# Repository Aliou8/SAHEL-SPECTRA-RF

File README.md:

# SAHEL-CUBESAT: An Experimental Educational CubeSat 
# Project work in progress

This project aims to develop a complete experimental CubeSat for educational purposes. It is based on an STM32H7 MCU for data handling and uses two CC1200 radios for communication. The software is developed using a Zephyr-like RTOS.

<table>  <tr>    <td align="center">      <br>      <b>Mechanical Frame</b>    </td>    <td align="center">      <br>      <b>CubeSat Assembly with PCBs</b>    </td>    <td align="center">      <br>      <b>Complete CubeSat Assembly</b>    </td>  </tr></table>

## Table of Contents

- [Hardware](#hardware)
  - [Structure](#structure)
  - [Electronics](#electronics)
    - [Radio and OBC PCB](#radio-and-obc-pcb)
    - [Solar Panel and Battery PCB](#solar-panel-and-battery-pcb)

- [Software](#software)
  - [System Logic](#system-logic)
  - [Implementation](#implementation)

- [Ground Station Communication](#ground-station-communication)

---

## Hardware

### Structure

The structure was designed according to the specifications using [Onshape](https://cad.onshape.com?utm_source=chatgpt.com). All printable components can be found in this [directory](hardware/structure/).
<table>  <tr>    <td align="center">      <br>      <b>Mechanical faces X+ X- Y+ Y-</b>    </td>    <td align="center">      <br>      <b>Mechanical faces Z+ Z-</b>    </td>    <td align="center">      <br>      <b> Solar panel</b>    </td>  </tr></table>

---

### Electronics

KiCad is used for the electronic design. The hardware is divided into three parts. The first part includes the radio communication system and the OBC (On-Board Computer) for the CubeSat. The second part consists of a board integrating several sensors and a solar MPPT controller IC.

#### Radio and OBC PCB : Available in: [hardware/sahel_pcb_main](hardware/sahel_pcb_main/)

<table>
  <tr>
    <td align="center">
      <br>
      <b>Architectural Diagram of the Radio and OBC PCB</b>
    </td>
    <td align="center">
      <br>
      <b>Radio and OBC PCB</b>
    </td>
  </tr>
</table>

---

##### Components

###### MCU

**STM32H7B0VBTx**  
High-performance Arm Cortex-M7 MCU with DSP and DP-FPU, 128 KB Flash, 1,376 KB SRAM, up to 280 MHz.

---

###### FRAM — FM24CL64B

| Parameter        | Value            |
|-----------------|------------------|
| Memory          | 64-Kbit (8K × 8) |
| I2C Address      | `0b1010000`        |
| SDA (I2C3)       | PC9              |
| SCL (I2C3)       | PA8              |
| Write Protect    | PC5              |

###### Sensors

**Accelerometer, Gyroscope, and Magnetometer: LSM9DS1**  
**Barometer: BMP388**

| Parameter            | Value        |
|---------------------|-------------|
| I2C Address (ACC/GYRO) | `0b1101011` |
| I2C Address (MAG)      | `0b0011110` |
| I2C Address (BARO)     | `0b1110111` |
| SDA (I2C4)             | PD13        |
| SCL (I2C4)             | PD12        |
| INT_ACC/GYRO           | PE8         |
| DRDY_MAG               | PE7         |
| DRDY_BARO              | PB2         |
---

###### RTC & Temperature Sensor

**RTC: RV-8803-C7**  
**TEMP: TMP100**

| Parameter        | Value            |
|-----------------|------------------|
| RTC I2C Address  | `0b0110010`        |
| TEMP I2C Address | `0b1001000`        |
| SDA (I2C1)       | PB7              |
| SCL (I2C1)       | PB6              |
| RTC_INT          | PB5              |
| RTC_EVI          | PB4              |

---

###### CAN Interface: TCAN334G

| Signal     | Pin  |
|-----------|------|
| CAN1_TX    | PD1  |
| CAN1_RX    | PD0  |
| CAN_SHDN   | PA15 |
| CAN_STBY   | PD2  |

---

###### RS-485 Interface: ISL3170E

| Signal      | Pin  |
|------------|------|
| UART2_RX    | PD6  |
| UART2_TX    | PD5  |
| UART2_EN    | PD4  |

---
###### Radio Interface: CC1200

The CC1200 device is a fully integrated single-chip radio transceiver designed for high performance at very low-power and low-voltage operation in cost-effective wireless systems frequency bands at 164–192 MHz, 274–320 MHz, 410–480 MHz, and 820–960 MHz.

**UHF(TX/RX) 420-470 MHz**

| Signal      | Pin  |
|------------|------|
| UHF_SCK(SPI1)    | PA5  |
| UHF_MISO(SPI1)     | P6  |
| UHF_MOSI(SPI1)     | P7  |
| UHF_CS(SPI1)     | PA4  |
| UHF_GPIO2    | PC5  |
| UHF_GPIO3    | PC4  |

**VHF(TX/RX) 164-192 MHz**

| Signal      | Pin  |
|------------|------|
| UHF_SCK(SPI4)    | PE12  |
| UHF_MISO(SPI4)     | PE13  |
| UHF_MOSI(SPI4)     | PE14  |
| UHF_CS(SPI4)     | PE11  |
| UHF_GPIO2    | PB10  |
| UHF_GPIO3    | PE14  |

#### Solar Panel and Battery PCB

<table>
  <tr>
    <td align="center">
      <br>
      <b> Solar charger PCB </b>      
    </td>
    <td align="center">
      <br>
      <b> Battery charger PCB </b>
    </td>
  </tr>
</table>

In this project, the BQ24650 solar charger is used together with an INA219A current sensor for photovoltaic (IPV) monitoring.

| Parameter                  | Value               |
|---------------------------|---------------------|
| Input Voltage (Vin)       | 9V – 24V            |
| MPPT Voltage (VMPPT)      | 9V                  |
| Charge Voltage            | 8.2V                |
| Charge Current            | 1.2A                |
| Precharge Current         | 125mA               |
| Termination Current       | 125mA               |
| INA219A I2C Address       | `0b1000010`         |
| SDA (I2C4)                | PD13                |
| SCL (I2C4)                | PD12                |

---

### Battery Pack & Protection

The system uses four RS PRO Li-Ion batteries configured in a 2S2P arrangement with the following specifications:

| Parameter                          | Value                |
|-----------------------------------|----------------------|
| Nominal Voltage                   | 3.60V                |
| Capacity                          | 3500mAh              |
| Maximum Charge Voltage            | 4.20V                |
| Energy                            | 12.60Wh              |
| Operating Voltage                 | 4.20V – 2.50V        |
| Cut-Off Voltage                   | 2.50V                |
| Standard Charge Method            | CC-CV                |
| Standard Charge Current           | 0.2C (0.7A)          |
| Standard Charge Cut-Off Current   | 0.02C (0.07A)        |
| Maximum Continuous Charge Current | 1.0C (3.5A)          |

#### Standard Discharge Conditions

| Temperature Range | Discharge Current |
|------------------|------------------|
| 0°C – 10°C       | 0.1C (0.35A)     |
| 10°C – 20°C      | 0.2C (0.7A)      |
| 20°C – 45°C      | 0.5C (1.75A)     |

The battery protection and monitoring system is based on the BQ76907 battery monitor IC and an INA219A current sensor.

| Parameter              | Value                    |
|-----------------------|--------------------------|
| I2C Address (BQ76907) | `0b0001000` (default)    |
| I2C Address (INA219A) | `0b1000000`              |
| SDA (I2C1)            | PB7                      |
| SCL (I2C1)            | PB6                      |
| Battery Alert         | PE2                      |

---

## Software

The software is developed using **Zephyr RTOS**.  
The middleware architecture is described in the [Software Documentation](software/README.md).

---

## System Logic

We are developing the system based on **Zephyr RTOS**, using a **multi-threaded architecture** combined with **Zephyr zbus** for internal communication.

The application is structured around multiple independent threads that communicate through the **zbus message bus system**.

### Key concepts:
- Each module acts as a **zbus publisher and/or subscriber**
- Data is exchanged through **well-defined channels**
- This avoids tight coupling between components
- Improves scalability and modularity of the system

### Benefits of using zbus:
- Decoupled architecture between threads
- Clean publish/subscribe communication model
- Easier debugging and tracing of data flow
- Better maintainability for complex systems

---

## Ground Station Communication

The ground station software is **not yet implemented**.  
The current plan is to develop it using either:
- **Qt-based applications** (for a custom GUI control station)
- or existing **SDR software tools** for signal reception and analysis

---

## Communication Mechanism

The communication between the system and the ground station is designed around a structured and layered protocol stack.

### 1. Physical & Link Layer
The system uses the **AX.25 protocol** as the primary data link layer.

AX.25 provides:
- reliable packet framing
- addressing capability (callsigns)
- error detection (CRC)
- compatibility with amateur radio / SDR systems

---

### 2. Packet Structure

All exchanged data is encapsulated in AX.25 frames containing:
- payload data
- message type identifier
- optional sequence number
- checksum (handled by AX.25 layer)

---

### 3. Command System

The ground station can send **commands** to the embedded system.

Commands are structured as:
- command ID
- optional parameters
- target module (if applicable)

Examples of command types:
- system control (start / stop / reset)
- configuration update
- request sensor data
- debug / diagnostics requests

---

### 4. Internal Routing (zbus integration)

Incoming and outgoing messages are bridged into the internal **zbus architecture**.

Flow:
- AX.25 frame received → decoded → converted to internal message
- message published on **zbus channel**
- relevant modules subscribe and react

---

### 5. Response System

The system responds using structured messages:
- ACK / NACK for command validation
- telemetry data packets
- event notifications
- status reports

All responses follow the same pipeline:
**zbus → encoder → AX.25 → ground station**

---

### 6. Design Goals

This architecture is designed to ensure:
- robustness over noisy RF links
- modular separation between communication and logic
- easy integration with SDR tools
- future compatibility with different ground station implementations

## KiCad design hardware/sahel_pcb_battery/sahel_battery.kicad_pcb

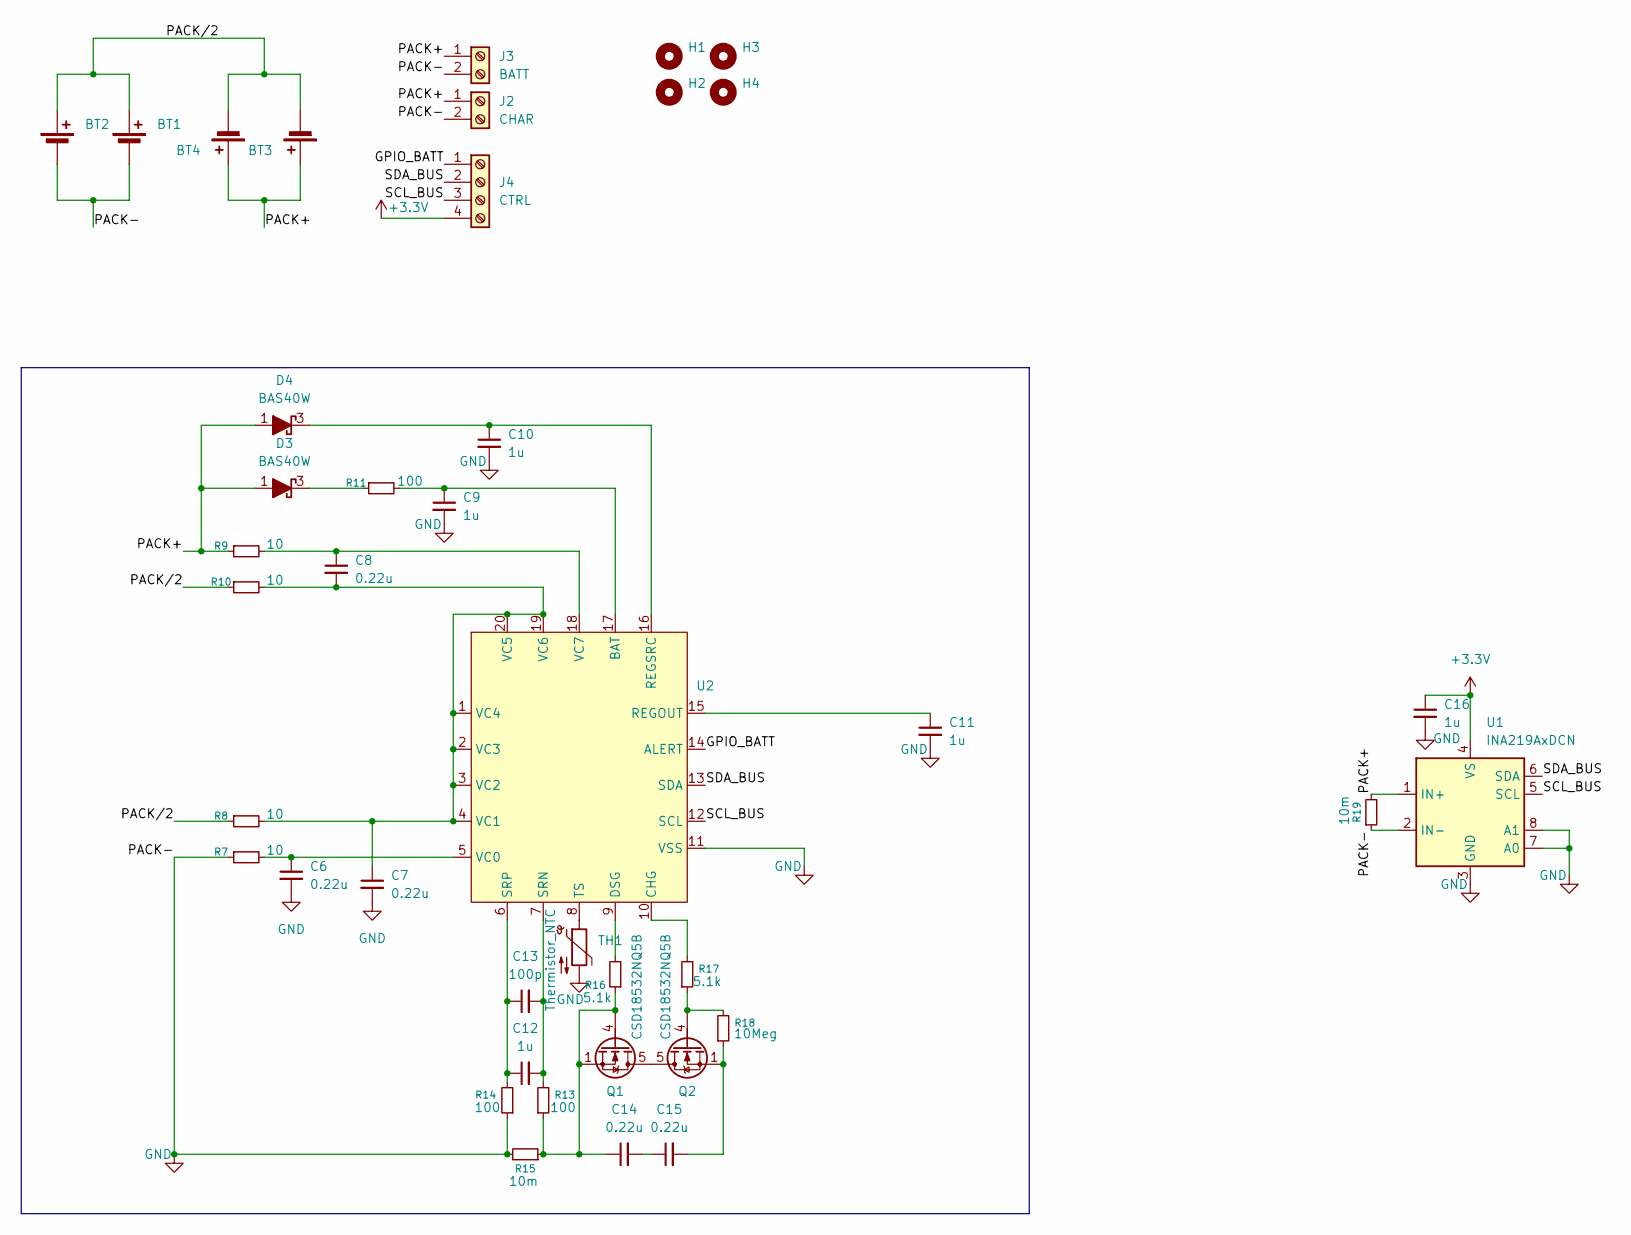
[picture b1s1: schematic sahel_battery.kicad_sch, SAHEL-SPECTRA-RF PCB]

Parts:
BT1, BT2, BT3, BT4: Battery_Cell; BatteryHolder_Keystone_1042_1x18650
C6, C7, C8, C14, C15: 0.22u; C_0805_2012Metric
C9, C10, C12: 1u; C_0805_2012Metric
C11, C16: 1u; C_0402_1005Metric
C13: 100p; C_0805_2012Metric
D3, D4: BAS40W; SOT-323_SC-70
H1, H2, H3, H4: MountingHole; MountingHole_2.5mm
J2: CHAR; JST_PH_B2B-PH-K_1x02_P2.00mm_Vertical
J3: BATT; JST_PH_B2B-PH-K_1x02_P2.00mm_Vertical
J4: CTRL; JST_PH_B4B-PH-K_1x04_P2.00mm_Vertical
Q1, Q2: CSD18532NQ5B; TDSON-8-1
R7, R8, R9, R10: 10; R_0805_2012Metric
R11, R13, R14: 100; R_0805_2012Metric
R15, R19: 10m; R_1206_3216Metric
R16, R17: 5.1k; R_0805_2012Metric
R18: 10Meg; R_0805_2012Metric
TH1: Thermistor_NTC; RV_Disc_D7mm_W3.4mm_P5mm
U1: INA219AxDCN; SOT-23-8
U2: QFN-20-1EP_3.5x3.5mm_P0.5mm_EP2x2mm

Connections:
+3.3V: C16.1, J4.4, U1.4 (VS)
/GPIO_BATT: J4.1, U2.14 (ALERT)
/PACK+: BT3.1 (+), BT4.1 (+), D3.1 (A), D4.1 (A), J2.1, J3.1, R9.1, R19.2, U1.1 (IN+)
/PACK/2: BT1.1 (+), BT2.1 (+), BT3.2 (-), BT4.2 (-), R8.1, R10.1
/SCL_BUS: J4.3, U1.5 (SCL), U2.12 (SCL)
/SDA_BUS: J4.2, U1.6 (SDA), U2.13 (SDA)
GND: BT1.2 (-), BT2.2 (-), C6.2, C7.2, C9.2, C10.2, C11.2, C16.2, J2.2, J3.2, R7.1, R14.1, R15.2, R19.1, TH1.2, U1.2 (IN-), U1.3 (GND), U1.7 (A0), U1.8 (A1), U2.11 (VSS), U2.21 (PAD)
unnamed: C14.2, C15.1
unnamed: C15.2, Q2.1 (S), Q2.2 (S), Q2.3 (S), R18.1
unnamed: D3.3 (K), R11.1
unnamed: C10.1, D4.3 (K), U2.16 (REGSRC)
unnamed: Q1.5 (D), Q2.5 (D)
unnamed: C14.1, Q1.1 (S), Q1.2 (S), Q1.3 (S), Q1.4 (G), R13.1, R15.1, R16.1
unnamed: Q2.4 (G), R17.1, R18.2
unnamed: C9.1, R11.2, U2.17 (BAT)
unnamed: R17.2, U2.10 (CHG)
unnamed: R16.2, U2.9 (DSG)
unnamed: C11.1, U2.15 (REGOUT)
unnamed: C12.2, C13.2, R13.2, U2.7 (SRN)
unnamed: C12.1, C13.1, R14.2, U2.6 (SRP)
unnamed: TH1.1, U2.8 (TS)
unnamed: C6.1, R7.2, U2.5 (VC0)
unnamed: C7.1, C8.2, R8.2, R10.2, U2.1 (VC4), U2.2 (VC3), U2.3 (VC2), U2.4 (VC1), U2.19 (VC6), U2.20 (VC5)
unnamed: C8.1, R9.2, U2.18 (VC7)

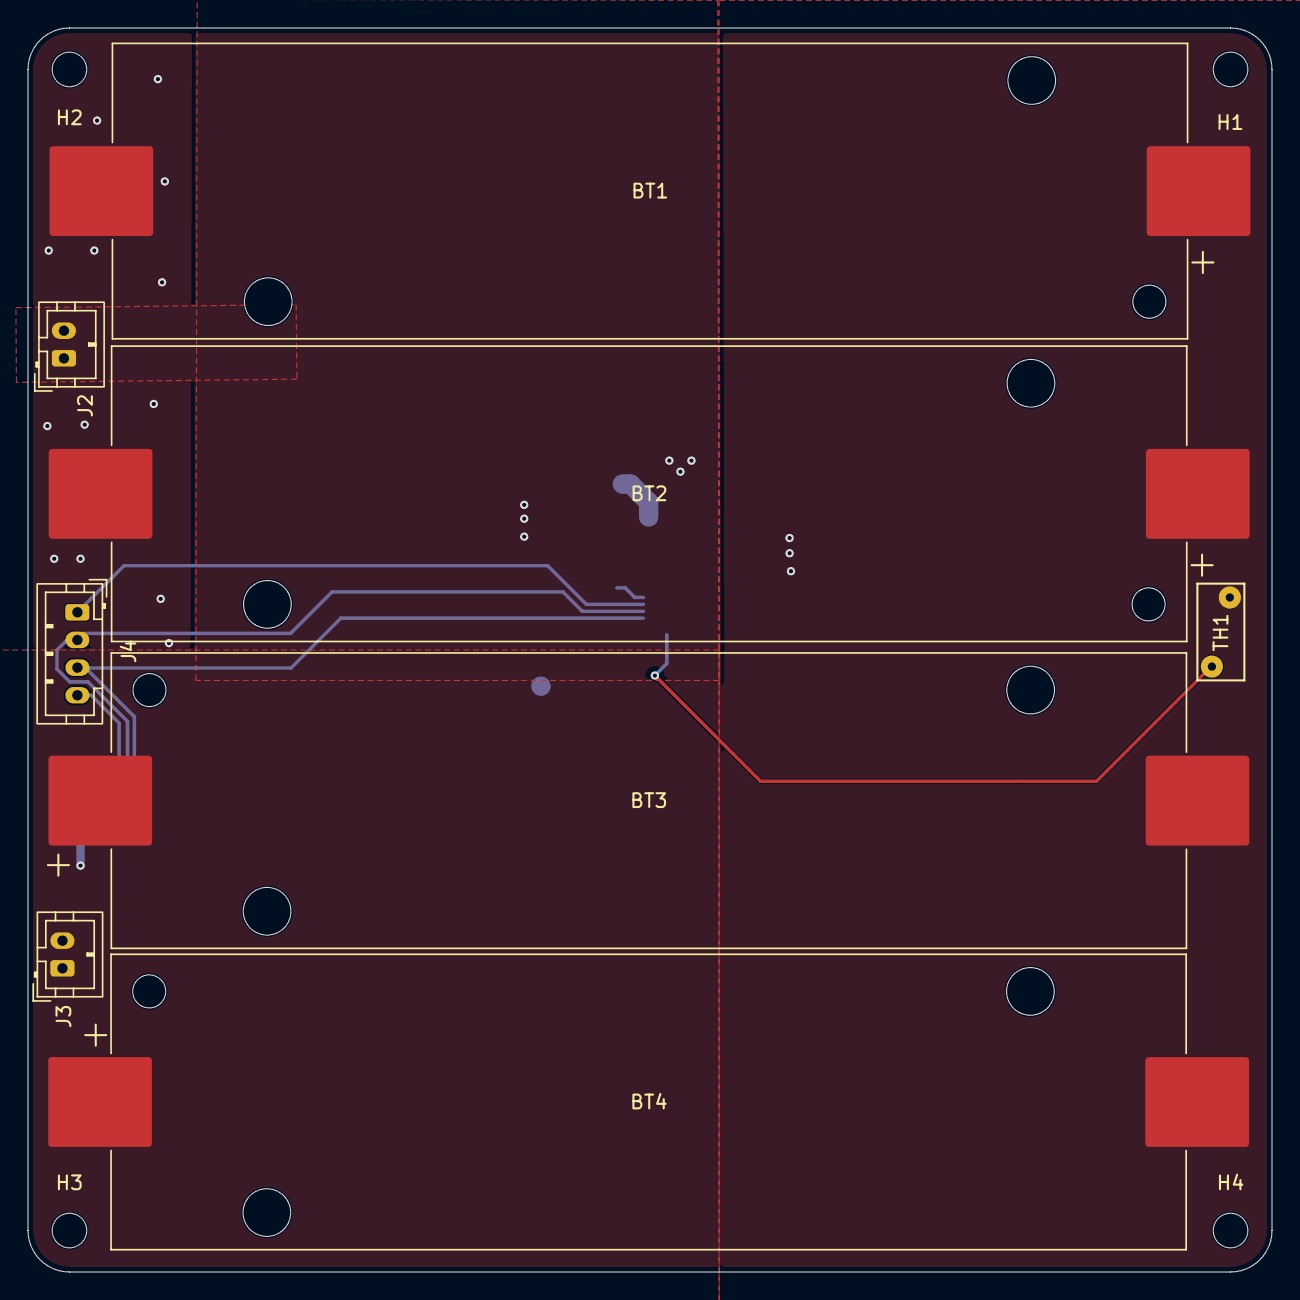
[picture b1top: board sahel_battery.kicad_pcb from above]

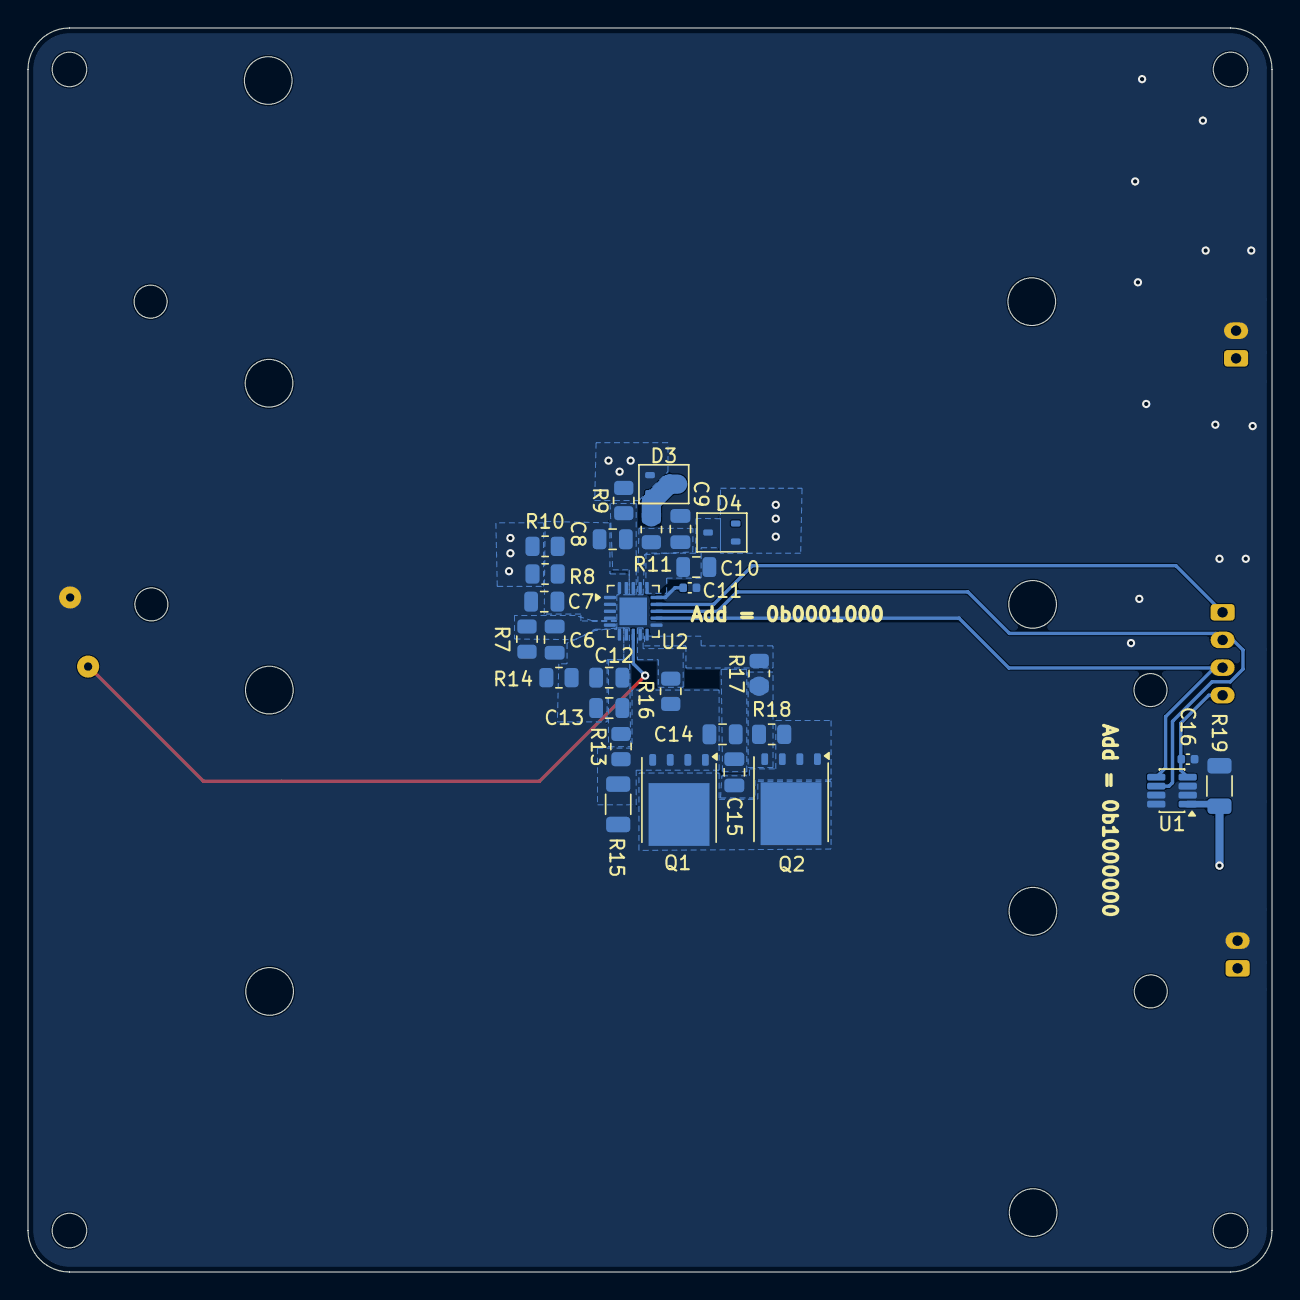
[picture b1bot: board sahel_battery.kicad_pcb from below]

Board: 2 copper layers, 90.0 x 90.0 mm, 41 parts (29 on the bottom side), 24 nets.

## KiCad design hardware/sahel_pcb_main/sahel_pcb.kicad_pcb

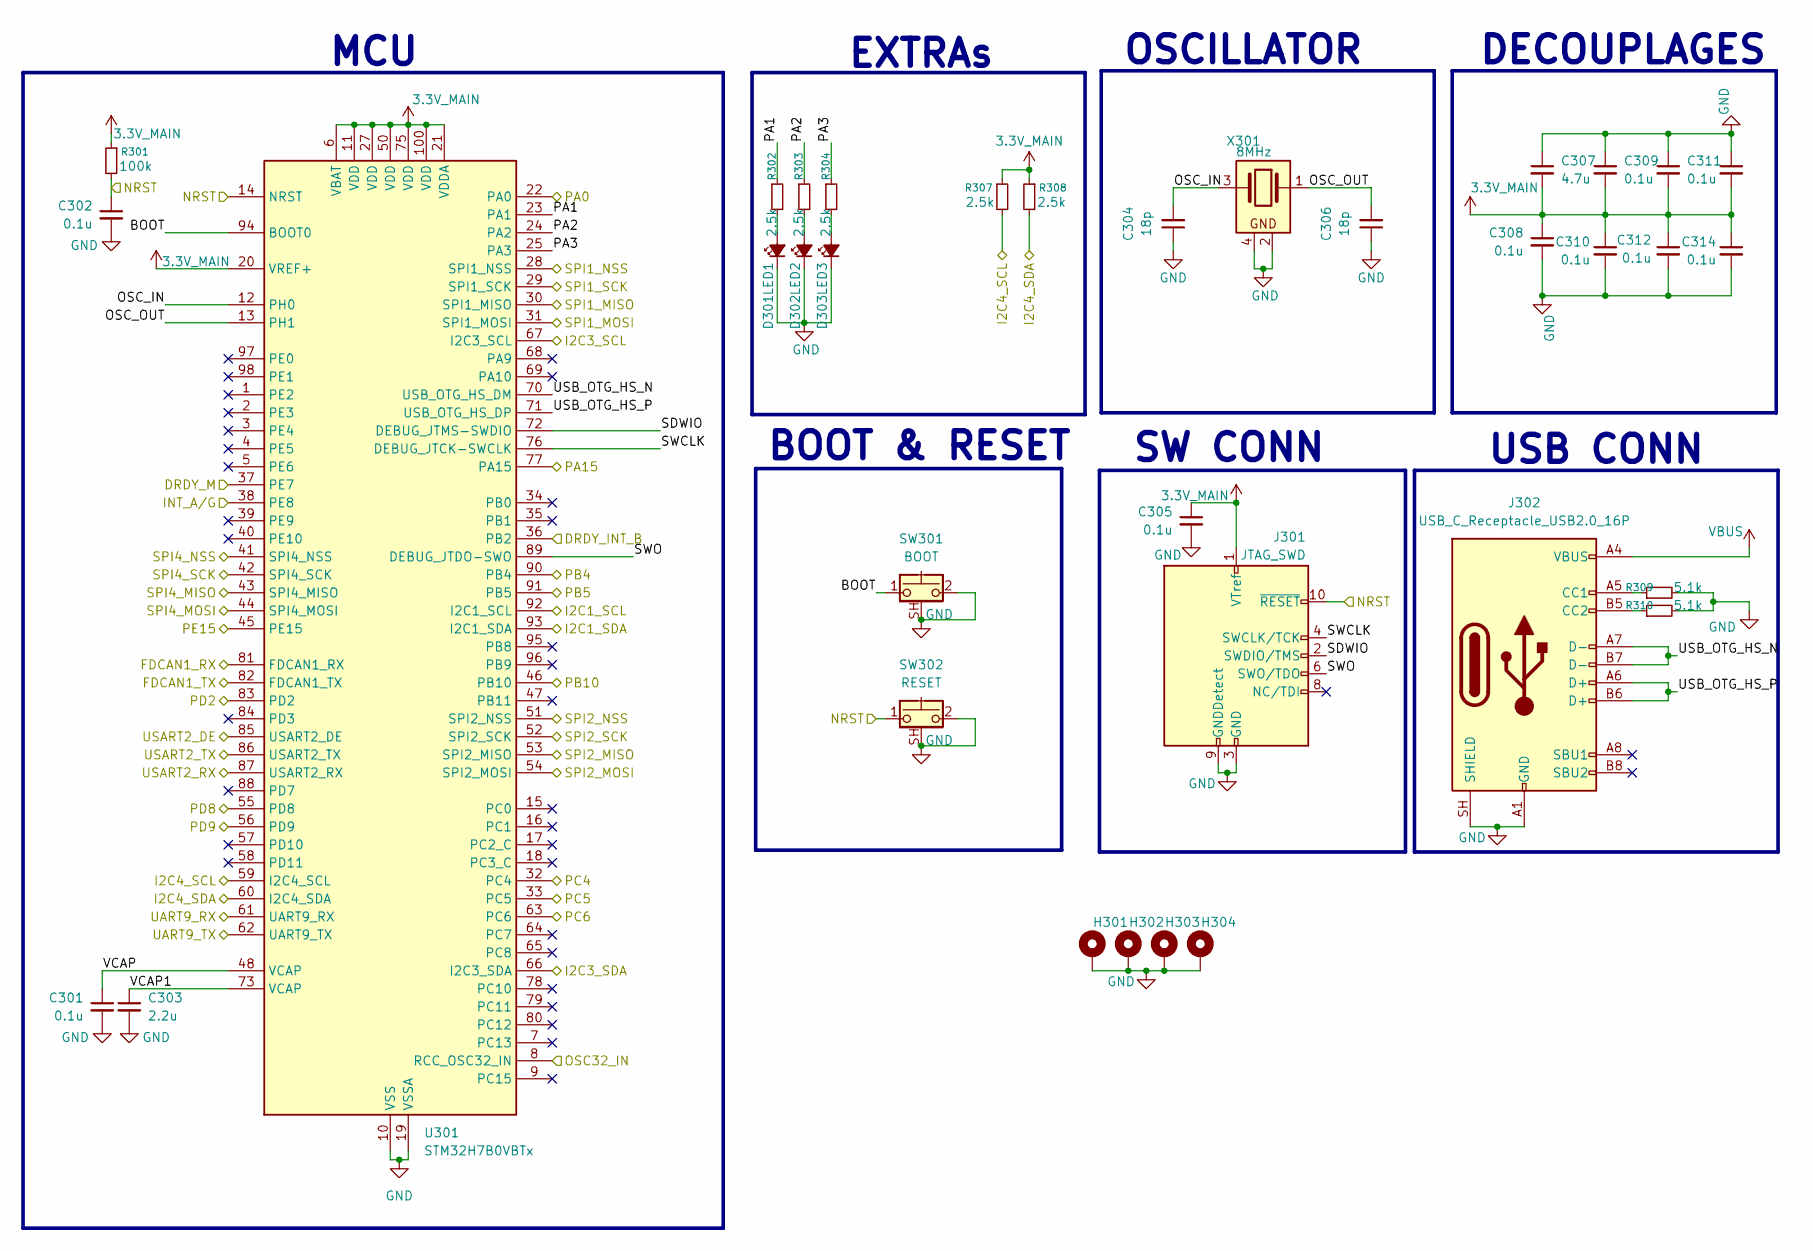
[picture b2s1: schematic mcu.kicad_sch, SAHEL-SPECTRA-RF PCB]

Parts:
C301, C302, C305, C308, C309, C310, C311, C312, C313, C314: 0.1u; C_0402_1005Metric
C303: 2.2u; C_0402_1005Metric
C304, C306: 18p; C_0402_1005Metric
C307: 4.7u; C_0402_1005Metric
D301: LED1; LED_0402_1005Metric
D302: LED2; LED_0402_1005Metric
D303: LED3; LED_0402_1005Metric
H301, H302, H303, H304: MountingHole_Pad; MountingHole_2.2mm_M2_Pad
J301: JTAG_SWD; PinHeader_2x05_P1.27mm_Vertical
J302: USB_C_Receptacle_USB2.0_16P; USB_C_Receptacle_GCT_USB4105-xx-A_16P_TopMnt_Horizontal
R301: 100k; R_0402_1005Metric
R302, R303, R304, R307, R308: 2.5k; R_0402_1005Metric
R309, R310: 5.1k; R_0402_1005Metric
SW301: BOOT; SW_SPST_CK_KMS2xxGP
SW302: RESET; SW_SPST_CK_KMS2xxGP
U301: STM32H7B0VBTx; LQFP-100_14x14mm_P0.5mm
X301: 8MHz; Crystal_SMD_2520-4Pin_2.5x2.0mm

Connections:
3.3V_MAIN: C305.1, C307.2, C308.1, C309.2, C310.1, C311.2, C312.1, C313.2, C314.1, J301.1 (VTref), R301.1, R307.1, R308.1, U301.6 (VBAT), U301.11 (VDD), U301.20 (VREF+), U301.21 (VDDA), U301.27 (VDD), U301.50 (VDD), U301.75 (VDD), U301.100 (VDD); also elsewhere on the board
/BUS_SCL: R307.2, U301.59 (I2C4_SCL); also elsewhere on the board
/BUS_SDA: R308.2, U301.60 (I2C4_SDA); also elsewhere on the board
/BUS_UART_RX: U301.61 (UART9_RX); also elsewhere on the board
/BUS_UART_TX: U301.62 (UART9_TX); also elsewhere on the board
/DRDY_INT_B: U301.36 (PB2); also elsewhere on the board
/DRDY_M: U301.37 (PE7); also elsewhere on the board
/INT_A/G: U301.38 (PE8); also elsewhere on the board
/MCU/BOOT: SW301.1, U301.94 (BOOT0)
/MCU/FDCAN1_RX: U301.81 (FDCAN1_RX); also elsewhere on the board
/MCU/FDCAN1_TX: U301.82 (FDCAN1_TX); also elsewhere on the board
/MCU/I2C3_SCL: U301.67 (I2C3_SCL); also elsewhere on the board
/MCU/I2C3_SDA: U301.66 (I2C3_SDA); also elsewhere on the board
/MCU/NRST: C302.1, J301.10 (~RESET), R301.2, SW302.1, U301.14 (NRST); also elsewhere on the board
/MCU/OSC32_IN: U301.8 (RCC_OSC32_IN); also elsewhere on the board
/MCU/OSC_IN: C304.2, U301.12 (PH0), X301.3
/MCU/OSC_OUT: C306.2, U301.13 (PH1), X301.1
/MCU/PA0: U301.22 (PA0); also elsewhere on the board
/MCU/PA1: R302.1, U301.23 (PA1)
/MCU/PA2: R303.1, U301.24 (PA2)
/MCU/PA3: R304.1, U301.25 (PA3)
/MCU/PA15: U301.77 (PA15); also elsewhere on the board
/MCU/PB4: U301.90 (PB4); also elsewhere on the board
/MCU/PB5: U301.91 (PB5); also elsewhere on the board
/MCU/PB10: U301.46 (PB10); also elsewhere on the board
/MCU/PC4: U301.32 (PC4); also elsewhere on the board
/MCU/PC5: U301.33 (PC5); also elsewhere on the board
/MCU/PC6: U301.63 (PC6); also elsewhere on the board
/MCU/PD2: U301.83 (PD2); also elsewhere on the board
/MCU/PE15: U301.45 (PE15); also elsewhere on the board
/MCU/SDWIO: J301.2 (SWDIO/TMS), U301.72 (DEBUG_JTMS-SWDIO)
/MCU/SPI1_MISO: U301.30 (SPI1_MISO); also elsewhere on the board
/MCU/SPI1_MOSI: U301.31 (SPI1_MOSI); also elsewhere on the board
/MCU/SPI1_NSS: U301.28 (SPI1_NSS); also elsewhere on the board
/MCU/SPI1_SCK: U301.29 (SPI1_SCK); also elsewhere on the board
/MCU/SPI4_MISO: U301.43 (SPI4_MISO); also elsewhere on the board
/MCU/SPI4_MOSI: U301.44 (SPI4_MOSI); also elsewhere on the board
/MCU/SPI4_NSS: U301.41 (SPI4_NSS); also elsewhere on the board
/MCU/SPI4_SCK: U301.42 (SPI4_SCK); also elsewhere on the board
/MCU/SWCLK: J301.4 (SWCLK/TCK), U301.76 (DEBUG_JTCK-SWCLK)
/MCU/SWO: J301.6 (SWO/TDO), U301.89 (DEBUG_JTDO-SWO)
/MCU/USART2_DE: U301.85 (USART2_DE); also elsewhere on the board
/MCU/USART2_RX: U301.87 (USART2_RX); also elsewhere on the board
/MCU/USART2_TX: U301.86 (USART2_TX); also elsewhere on the board
/MCU/USB_OTG_HS_N: J302.A7 (D-), J302.B7 (D-), U301.70 (USB_OTG_HS_DM)
/MCU/USB_OTG_HS_P: J302.A6 (D+), J302.B6 (D+), U301.71 (USB_OTG_HS_DP)
/MCU/VCAP: C301.1, U301.48 (VCAP)
/MCU/VCAP1: C303.1, U301.73 (VCAP)
/SPI_CS: U301.51 (SPI2_NSS); also elsewhere on the board
/SPI_CS1: U301.55 (PD8); also elsewhere on the board
/SPI_CS2: U301.56 (PD9); also elsewhere on the board
/SPI_MISO: U301.53 (SPI2_MISO); also elsewhere on the board
/SPI_MOSI: U301.54 (SPI2_MOSI); also elsewhere on the board
/SPI_SCK: U301.52 (SPI2_SCK); also elsewhere on the board
/_SCL: U301.92 (I2C1_SCL); also elsewhere on the board
/_SDA: U301.93 (I2C1_SDA); also elsewhere on the board
/bat_alert: U301.1 (PE2); also elsewhere on the board
GND: C301.2, C302.2, C303.2, C304.1, C305.2, C306.1, C307.1, C308.2, C309.1, C310.2, C311.1, C312.2, C313.1, C314.2, D301.1 (K), D302.1 (K), D303.1 (K), H301.1 (1_1), H302.1 (1_1), H303.1 (1_1), H304.1 (1_1), J301.3 (GND), J301.5 (GND), J301.9 (GNDDetect), J302.A1 (GND), J302.A12 (GND), J302.B1 (GND), J302.B12 (GND), J302.SH (SHIELD), R309.2, R310.2, SW301.2, SW301.SH (B), SW302.2, SW302.SH (B), U301.10 (VSS), U301.19 (VSSA), U301.26 (VSS), U301.49 (VSS), U301.74 (VSS), U301.99 (VSS), X301.2, X301.4; also elsewhere on the board
unnamed: D301.2 (A), R302.2
unnamed: D302.2 (A), R303.2
unnamed: D303.2 (A), R304.2
unnamed: J302.A5 (CC1), R309.1
unnamed: J302.B5 (CC2), R310.1
VBUS: J302.A4 (VBUS), J302.A9 (VBUS), J302.B4 (VBUS), J302.B9 (VBUS); also elsewhere on the board

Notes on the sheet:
MCU
USB CONN
EXTRAs
DECOUPLAGES
SW CONN
OSCILLATOR
BOOT & RESET

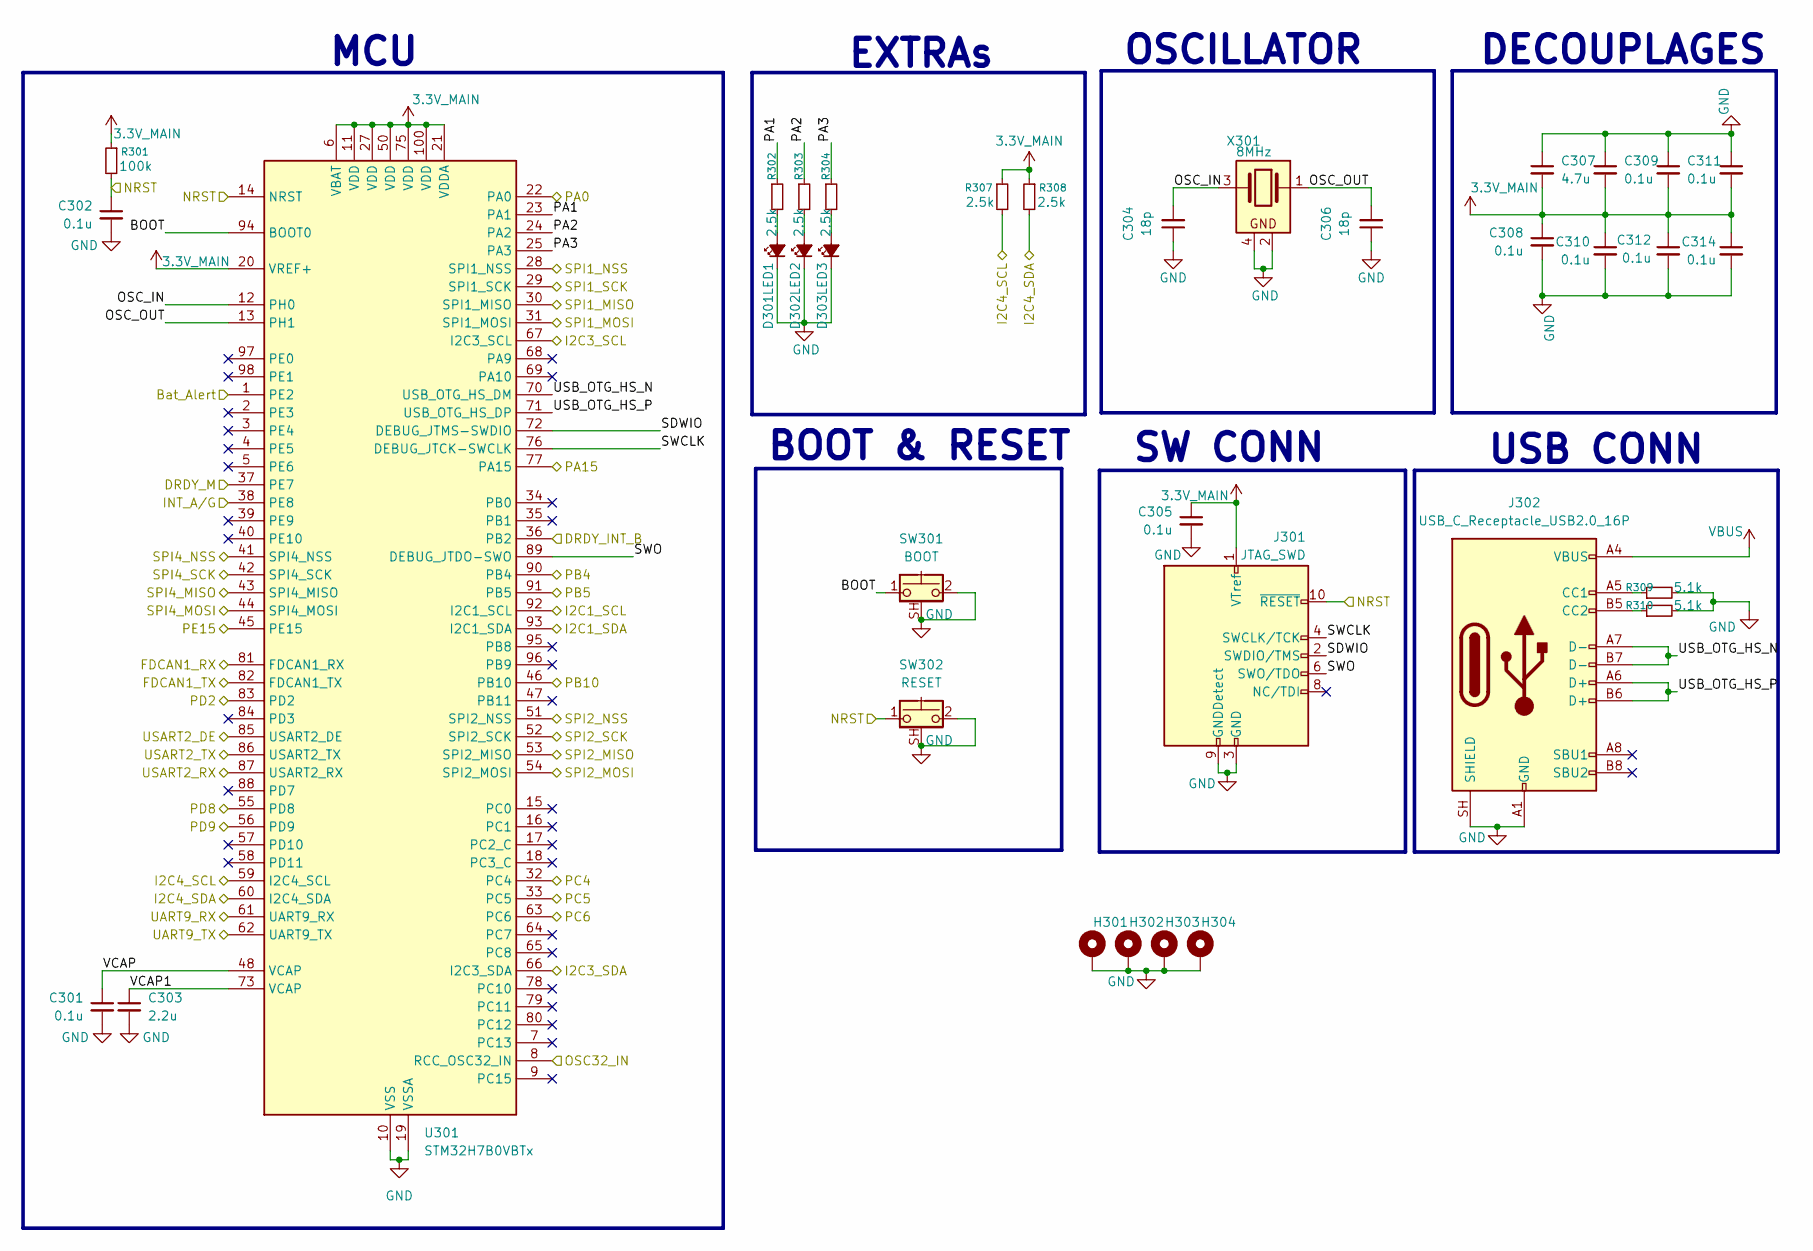
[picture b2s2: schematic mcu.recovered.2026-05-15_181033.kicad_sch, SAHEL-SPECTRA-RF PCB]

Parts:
C301, C302, C305, C308, C309, C310, C311, C312, C313, C314: 0.1u; C_0402_1005Metric
C303: 2.2u; C_0402_1005Metric
C304, C306: 18p; C_0402_1005Metric
C307: 4.7u; C_0402_1005Metric
D301: LED1; LED_0402_1005Metric
D302: LED2; LED_0402_1005Metric
D303: LED3; LED_0402_1005Metric
H301, H302, H303, H304: MountingHole_Pad; MountingHole_2.2mm_M2_Pad
J301: JTAG_SWD; PinHeader_2x05_P1.27mm_Vertical
J302: USB_C_Receptacle_USB2.0_16P; USB_C_Receptacle_GCT_USB4105-xx-A_16P_TopMnt_Horizontal
R301: 100k; R_0402_1005Metric
R302, R303, R304, R307, R308: 2.5k; R_0402_1005Metric
R309, R310: 5.1k; R_0402_1005Metric
SW301: BOOT; SW_SPST_CK_KMS2xxGP
SW302: RESET; SW_SPST_CK_KMS2xxGP
U301: STM32H7B0VBTx; LQFP-100_14x14mm_P0.5mm
X301: 8MHz; Crystal_SMD_2520-4Pin_2.5x2.0mm

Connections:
3.3V_MAIN: C305.1, C307.2, C308.1, C309.2, C310.1, C311.2, C312.1, C313.2, C314.1, J301.1 (VTref), R301.1, R307.1, R308.1, U301.6 (VBAT), U301.11 (VDD), U301.20 (VREF+), U301.21 (VDDA), U301.27 (VDD), U301.50 (VDD), U301.75 (VDD), U301.100 (VDD); also elsewhere on the board
/BUS_SCL: R307.2, U301.59 (I2C4_SCL); also elsewhere on the board
/BUS_SDA: R308.2, U301.60 (I2C4_SDA); also elsewhere on the board
/BUS_UART_RX: U301.61 (UART9_RX); also elsewhere on the board
/BUS_UART_TX: U301.62 (UART9_TX); also elsewhere on the board
/DRDY_INT_B: U301.36 (PB2); also elsewhere on the board
/DRDY_M: U301.37 (PE7); also elsewhere on the board
/INT_A/G: U301.38 (PE8); also elsewhere on the board
/MCU/BOOT: SW301.1, U301.94 (BOOT0)
/MCU/FDCAN1_RX: U301.81 (FDCAN1_RX); also elsewhere on the board
/MCU/FDCAN1_TX: U301.82 (FDCAN1_TX); also elsewhere on the board
/MCU/I2C3_SCL: U301.67 (I2C3_SCL); also elsewhere on the board
/MCU/I2C3_SDA: U301.66 (I2C3_SDA); also elsewhere on the board
/MCU/NRST: C302.1, J301.10 (~RESET), R301.2, SW302.1, U301.14 (NRST); also elsewhere on the board
/MCU/OSC32_IN: U301.8 (RCC_OSC32_IN); also elsewhere on the board
/MCU/OSC_IN: C304.2, U301.12 (PH0), X301.3
/MCU/OSC_OUT: C306.2, U301.13 (PH1), X301.1
/MCU/PA0: U301.22 (PA0); also elsewhere on the board
/MCU/PA1: R302.1, U301.23 (PA1)
/MCU/PA2: R303.1, U301.24 (PA2)
/MCU/PA3: R304.1, U301.25 (PA3)
/MCU/PA15: U301.77 (PA15); also elsewhere on the board
/MCU/PB4: U301.90 (PB4); also elsewhere on the board
/MCU/PB5: U301.91 (PB5); also elsewhere on the board
/MCU/PB10: U301.46 (PB10); also elsewhere on the board
/MCU/PC4: U301.32 (PC4); also elsewhere on the board
/MCU/PC5: U301.33 (PC5); also elsewhere on the board
/MCU/PC6: U301.63 (PC6); also elsewhere on the board
/MCU/PD2: U301.83 (PD2); also elsewhere on the board
/MCU/PE15: U301.45 (PE15); also elsewhere on the board
/MCU/SDWIO: J301.2 (SWDIO/TMS), U301.72 (DEBUG_JTMS-SWDIO)
/MCU/SPI1_MISO: U301.30 (SPI1_MISO); also elsewhere on the board
/MCU/SPI1_MOSI: U301.31 (SPI1_MOSI); also elsewhere on the board
/MCU/SPI1_NSS: U301.28 (SPI1_NSS); also elsewhere on the board
/MCU/SPI1_SCK: U301.29 (SPI1_SCK); also elsewhere on the board
/MCU/SPI4_MISO: U301.43 (SPI4_MISO); also elsewhere on the board
/MCU/SPI4_MOSI: U301.44 (SPI4_MOSI); also elsewhere on the board
/MCU/SPI4_NSS: U301.41 (SPI4_NSS); also elsewhere on the board
/MCU/SPI4_SCK: U301.42 (SPI4_SCK); also elsewhere on the board
/MCU/SWCLK: J301.4 (SWCLK/TCK), U301.76 (DEBUG_JTCK-SWCLK)
/MCU/SWO: J301.6 (SWO/TDO), U301.89 (DEBUG_JTDO-SWO)
/MCU/USART2_DE: U301.85 (USART2_DE); also elsewhere on the board
/MCU/USART2_RX: U301.87 (USART2_RX); also elsewhere on the board
/MCU/USART2_TX: U301.86 (USART2_TX); also elsewhere on the board
/MCU/USB_OTG_HS_N: J302.A7 (D-), J302.B7 (D-), U301.70 (USB_OTG_HS_DM)
/MCU/USB_OTG_HS_P: J302.A6 (D+), J302.B6 (D+), U301.71 (USB_OTG_HS_DP)
/MCU/VCAP: C301.1, U301.48 (VCAP)
/MCU/VCAP1: C303.1, U301.73 (VCAP)
/SPI_CS: U301.51 (SPI2_NSS); also elsewhere on the board
/SPI_CS1: U301.55 (PD8); also elsewhere on the board
/SPI_CS2: U301.56 (PD9); also elsewhere on the board
/SPI_MISO: U301.53 (SPI2_MISO); also elsewhere on the board
/SPI_MOSI: U301.54 (SPI2_MOSI); also elsewhere on the board
/SPI_SCK: U301.52 (SPI2_SCK); also elsewhere on the board
/_SCL: U301.92 (I2C1_SCL); also elsewhere on the board
/_SDA: U301.93 (I2C1_SDA); also elsewhere on the board
/bat_alert: U301.1 (PE2); also elsewhere on the board
GND: C301.2, C302.2, C303.2, C304.1, C305.2, C306.1, C307.1, C308.2, C309.1, C310.2, C311.1, C312.2, C313.1, C314.2, D301.1 (K), D302.1 (K), D303.1 (K), H301.1 (1_1), H302.1 (1_1), H303.1 (1_1), H304.1 (1_1), J301.3 (GND), J301.5 (GND), J301.9 (GNDDetect), J302.A1 (GND), J302.A12 (GND), J302.B1 (GND), J302.B12 (GND), J302.SH (SHIELD), R309.2, R310.2, SW301.2, SW301.SH (B), SW302.2, SW302.SH (B), U301.10 (VSS), U301.19 (VSSA), U301.26 (VSS), U301.49 (VSS), U301.74 (VSS), U301.99 (VSS), X301.2, X301.4; also elsewhere on the board
unnamed: D301.2 (A), R302.2
unnamed: D302.2 (A), R303.2
unnamed: D303.2 (A), R304.2
unnamed: J302.A5 (CC1), R309.1
unnamed: J302.B5 (CC2), R310.1
VBUS: J302.A4 (VBUS), J302.A9 (VBUS), J302.B4 (VBUS), J302.B9 (VBUS); also elsewhere on the board

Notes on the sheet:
MCU
USB CONN
EXTRAs
DECOUPLAGES
SW CONN
OSCILLATOR
BOOT & RESET
